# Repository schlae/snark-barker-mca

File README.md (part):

# Snark Barker MCA - A Sound Blaster Compatible for Micro Channel Computers!

Do you desperately want a sound card for playing games on your Micro Channel-based IBM PS/2 computer--a system designed for serious business purposes? Do you not want to pay the ludicrous auction prices for the rare Sound Blaster MCV cards? Well, despair no longer: the Snark Barker MCA has arrived!

The Snark Barker MCA is a Sound Blaster-compatible sound card designed specifically for computers that use the Micro Channel bus. It supports Ad Lib synthesis, digital sound playback and recording, a standard PC joystick, and SB MIDI.

All of the components are readily available. In the bill of materials, Mouser part numbers are listed where available. The Yamaha synthesis chips may be obtained from a variety of sources in China, but they are not guaranteed to work, so I recommend getting 1 or 2 extras just in case. The same goes for the NE558. Note: A user reports that a Signetics NE558 with a date code of 8825VI that seems to be commonly available from China does not actually work. If you can't find any working 558 chips, try building [my replacement that uses four 555 chips](https://oshpark.com/shared_projects/zHGURt7g).

[Schematic](https://github.com/schlae/snark-barker-mca/blob/master/SnarkBarkerMCA.pdf)

[Bill of Materials](https://github.com/schlae/snark-barker-mca/blob/master/SnarkBarkerMCA.csv)

Please note that the 0.1" header pins are *not* listed on the BOM. They are standard breakaway headers. Headers J2, J4, J5, and J6 are optional and only useful for people who want to connect a logic analyzer to the bus for CPLD debugging.

The CMS chips U14 and U15 should not be installed since CMS functionality is not implemented at this time. Other devices listed as "DNI" are to be left empty with no component soldered in place.

Logic chips are all specified as AHCT, but ALS or ACT may also be used. Do not use LS or HCT devices, particularly for U2, since Micro Channel is a much faster bus than ISA and this logic is not quite fast enough to meet the timing margins. Bipolar families like F or S devices use excessive amounts of power but can be used in a pinch.

[Fab Files](https://github.com/schlae/snark-barker-mca/blob/master/fab/SnarkBarkerMCA-Rev2.zip)

## Fabrication Notes
This is a 4-layer board. The order of the two inner layers does not matter, but typically it goes F\_Cu, In1\_Cu, In2\_Cu, and B\_Cu. The board dimensions are 11.5 inches (292.1mm) by 3.475 inches (88.265mm).

When ordering the board, you **must** specify a card edge bevel of 20 degrees (details of the bevel are included in the Dwgs.User layer). This is **not** optional! The contacts in the Micro Channel socket are easily bent if you attempt to insert a card with no bevel. [Don't believe me? See this page.](https://www.ardent-tool.com/RS6000/RS6000_9-K.html#ECA265)

Ideally you should use selective gold plating (hard gold) for the edge fingers, but this can get expensive for small orders. ENIG will work but the gold will rub off fairly quickly.

For the soldermask color, pick whatever you want!

## Assembly Notes
I recommend soldering the CPLD (U31), the voltage regulator (U32), and the associated surface mount capacitors before you solder in the remaining components. You can do this by hand with a pencil iron or you can use a reflow process, but be aware that the board is too long to fit in the small hobbyist reflow ovens.

***Be sure the CPLD is soldered in the right way around! Compare it with my photo of the card to be sure you have it right!***

Inspect the CPLD's solder joints carefully with a microscope to make sure you don't have any bad connections or solder bridges. This can save you a lot of grief later on.

Install sockets for the Yamaha chips U9 and U10 in case you get one that doesn't work and need to replace it.

## Bracket
MCA brackets are no longer available. You have a few options:
- Remove the brackets from an existing card, like a token ring card or something common
- 3D print the bracket
- Use the card without a bracket at all

If you want to print your own brackets, here are STL files of the front panel bracket and the rear bracket.

[Front bracket](https://github.com/schlae/snark-barker-mca/blob/master/mech/SnarkBarkerMCABracket3D.STL)

[Rear bracket](https://github.com/schlae/snark-barker-mca/blob/master/mech/MCARearBracket.STL)

For best results, use high quality filament and a layer height of 0.16mm or better. If you print using blue filament, the color will match the original IBM brackets.

The front bracket should be oriented so that the front face of the bracket is facing towards the bed of the printer. The rear bracket should be oriented so its large flat spot (parallel to the card) faces the bed.

To secure the bracket to the card, you need two screws, and you have several options:
- 2-56 pan-head screws, 3/16" long, McMaster Carr 91772A076 or similar. These work but aren't the strongest.
- Number 2 thread forming screws, 3/16" long, McMaster Carr 99461A710 or similar. These should grip the plastic tightly (TODO: untested).
- There may be equivalent metric options but this requires experimentation. Please let me know if you find a fastener that works well.

## The Firmware
There are two ways to get a programmed 80C51 chip for the Snark Barker MCA. One is to purchase a SB 2.0 DSP chip from China and put it in a 44-PLCC to 40-DIP adapter. This works fine and provides the largest feature set.

Another option is to buy a blank Atmel 89S51 (as listed in the BOM) and program it with [this HEX file](https://github.com/schlae/snark-barker/blob/master/firmware/sb.hex).

## CPLD Notes
The Snark Barker MCA uses a CPLD (Complex Programmable Logic Device) to interface between the Micro Channel bus and the rest of the card's digital logic. This CPLD implements port IO, interrupts, DMA, and the card setup and POS (Programmable Option Select) systems.

The CPLD must be programmed with the bitstream before you can use the card.
[You can find the bitstream here.](https://github.com/schlae/snark-barker-mca/blob/master/verilog/mcsb.jed)

I've had good luck using the Linux command line program 'xc3sprog' with a FTDI FT2232H Mini Module [datasheet here](https://www.ftdichip.com/Support/Documents/DataSheets/Modules/DS_FT2232H_Mini_Module.pdf).

Wiring for the FT2232H mini module:

| Point 1    | Point 2          | Description           |
| ---------- | ---------------- | --------------------- |
| CN2 pin 1  | CN2 pin 11       | V3V3 to VIO strap     |
| CN3 pin 1  | CN3 pin 3        | VBUS to VCC strap     |
| CN2 pin 3  | CN3 pin 12       | V3V3 to VIO strap (2) |
| CN2 pin 5  | JTAG cable pin 6 | V3V3 to Snark Barker (optional) |
| CN2 pin 2  | JTAG cable pin 5 | GND                   |
| CN2 pin 7  | JTAG cable pin 4 | AD0, aka TCK          |
| CN2 pin 9  | JTAG cable pin 3 | AD2, aka TDO          |
| CN2 pin 10 | JTAG cable pin 2 | AD1, aka TDI          |
| CN2 pin 12 | JTAG cable pin 1 | AD3, aka TMS          |

You need to provide external power to the Snark Barker through the 3.3V wire on the programming header. The optional wire does this, or you can use a bench supply.

I obtained xc3sprog [here](https://github.com/matrix-io/xc3sprog). You can compile and run this program on a Raspberry Pi to use the Pi GPIO lines instead of the FTDI mini module. In my case, I chose to patch it (TBD) to remove references to the Pi GPIO library and ran it on a regular Linux PC.

Using the FTDI mini module, programming is quite simple. Connect the cable to
the assembled Snark Barker board, then run the following command. You can do this with just the CPLD, programming header, and surface mount capacitors--there's no need to have any of the other components soldered in place for this step.

`xc3sprog -c ftdi -v mcadlib.jed`

If you run into issues with the cable not being detected, check your udev rules.
In theory you could run xc3sprog as root, but that's bad practice. ;)

### Building the CPLD Project
If you're feeling particularly masochistic, you can try building the CPLD project using the Xilinx ISE Webpack tools. Because the ISE Webpack only supports Ubuntu 14.7, it's simplest to run the program from a Docker container. I use [docker-xilinx](https://github.com/jimmo/docker-xilinx).

### How the CPLD Works
This isn't meant to be an exhaustive tutorial on how Micro Channel works ([you can find a tutorial here](https://github.com/schlae/mca-tutorial)). Functions provided by the CPLD include:
- Card setup and POS
- Address decoding logic
- Bus logic interface to the YM3812
- Wait state logic for the YM3812 interface
- Interrupt logic
- DMA state machine including arbitration logic

Each card implements several 8-bit registers (POS registers). Two of these registers are fixed and implement the 16-bit card ID value, which is how the BIOS and the reference disk software identify the card. The remaining POS registers can be used for any configuration-related function and are designed to replace configuration jumpers. The meanings of each register bit are up to the card designer, with the exception of a reserved bit that is used by the BIOS to enable or disable a card; this way, the BIOS can resolve conflicts automatically. Typically POS register bits control IO and memory address assignments, IRQ lines, and so forth.

The CPLD implements the two required ID registers as well as two additional POS registers. The first contains only a single bit -- the card enable signal. The second register controls the IO port setting, the IRQ and DMA channel settings, and the joystick port enable bit.

When you add a new card to a MCA bus system, the BIOS detects the new card and requires you to run the reference disk configuration program. This program searches for an ADF file associated with the new card. The ADF file is human-readable text that tells the BIOS which I/O address, IRQ, etc match up with each POS register bit. The reference disk program uses this information to find a configuration for all the cards in the computer so that none of them conflict with each other. When it's done, it writes the raw POS register values along with the card ID values to the battery-backed SRAM on the motherboard.

## Compatibility
The Snark Barker MCA has been tested on some models of PS/2. More to be added as
people provide test reports.

| Computer           | Model    | CPU          | Compatible ? |
| ------------------ | -------- | ------------ | ------------ |
| IBM PS/2 Model 50Z | 8550-031 | 80286-10     | Yes          |
| IBM PS/2 Model 55SX | 8555-X31 | 486SXLC2    | Yes          |
| IBM PS/2 Model 56  | 9556-KB6 | 80486SLC2-50 | Partial(1)   |
| IBM PS/2 Model 70  | 8570-E21 | 80386DX-16   | Yes          |
| IBM PS/2 Model 70  | 8570-B21 | 80486DX2-50  | Yes(1)       |
| IBM PS/2 Model P70 | 8573-061 | 80386DX-20   | Yes          |
| IBM PS/2 Model P75 | 8573-401 | 486DX2-66    | Yes(5)       |
| IBM PS/2 Model 80  | 8580-071 | 80386DX-16   | Yes(4)       |
| IBM PS/2 Model 95  | 8595     | 486DX2-50    | Yes(1)       |
| IBM PS/2 Model 95  | 9595     | Pentium-90   | Yes(3)       |
| NCR System 3400    | 3433     | 486DX2-66    | Yes          |
| NCR System 3400    | 3421     | 386SX-20     | Issues(2)    |

Note 1: See the *Machine Specific Notes* section below for more details about this configuration.

Note 2: Some problems reported with the NCR 3421 possibly due to a conflict with the onboard SCSI. Further investigation is needed.

Note 3: The Ad Lib detection routine used by some games is reported not to work

Note 4: There is one report of the Plaid Bib (the ancestor to this card) behaving erratically in this model of PS/2. However I have not observed any issues with the Snark Barker MCA.

Note 5: Machine has LAN Adapter/A installed.

If you build the card and try it out, please let me know how it went. **Be sure to give me the full part number of your computer along with any installed options (3rd-party planar, memory cards, etc).** If you're located in Silicon Valley, you could also loan me (or even give me!) a computer not on this list and I will test for compatibility myself.

## Machine Specific Notes

### IBM PS/2 Model 56 486SLC2 (9556-KB6)
Configuration: No cards installed.

The joystick port conflicts with the SCSI host that is built into the planar and must be disabled.

### IBM PS/2 Model 70 486 (8570-B21)
The configuration tested included
- 8MB RAM (on the planar)
- ESDI hard drive with DOS 6.22 and Windows 3.11 installed
- Buslogic BT640A SCSI card
- IBM XGA-2 video card

Although not fully understood, this configuration experiences what appear to be IRQ conflicts. The Micro Channel bus allows IRQ sharing, but not all software supports this correctly, so it may be related to that. "Doom" only works when using IRQ2. A workaround is to replace the default DOS4GW DOS extender with the DOS32A extender; this allows IRQ5 and IRQ7 to work correctly.

The Windows Sound Blaster driver crashes unless it is replaced with the driver recommended by Creative Labs for the SB Pro MCV. "VDMAD.386" is in the SB Pro MCV driver pack.

```
Some PS/2 machines experience a "Bus timeout error" when running Windows
3.1 in enhanced mode.  If you have this problem, Copy VDMAD.386 to your 
WINDOWS\SYSTEM sub-directory and change the following line under the [386Enh]
section in your SYSTEM.INI file.
[386Enh]
;change this line
DEVICE=*VDMAD
;to this line
DEVICE=VDMAD.386
```

You can also fix it by first starting Windows in standard mode, `win /s`, exit, and then start Windows in enhanced mode `win` as you normally would.

### IBM PS/2 Model 95 486DX2-50 (8595)
The joystick seems to conflict with something else and the setup program turns it off.

Getting Doom to run is slightly tricky and requires a hack. It only worked when IRQ was set to 5 and DOS4GW was replaced with DOS32A, but this version doesn't properly initialize the sound card. The hack is this:
- Make a copy of DOOM.EXE: `copy doom.exe doom_p.exe`
- Apply the DOS32A patch: `sb /r doom_p.exe`
- Run the original first: `doom` and let it crash back to the DOS prompt.
- Run the patched executable: `doom_p`

## Installation
You will need the ADF (adapter description file) in order to set up the Snark Barker MCA on your Micro Channel computer.

[Snark Barker MCA ADF](https://github.com/schlae/snark-barker-mca/blob/master/@5085.ADF)

Place the file on a 3 1/2" floppy disk. After you install the card and boot
the computer, it will detect that a new card has been installed and prompt
you to insert the reference disk. Do this and follow the prompts. When the
setup utility asks you to insert the option disk, use the one that contains
the ADF file. After the setup utility configures the card, it will prompt
you to reboot the machine.

Plug your line-level audio amplifier input into the card's 3mm audio jack nearest the joystick port. The other audio jack above that one is for the microphone input.

Once that's finished, try out the Snark Barker MCA with your favorite game!

## Troubleshooting
Hoo boy, this one is a doozie. Someone once told me
> At Creative Labs tech support we would always get a sinking feeling whenever someone said they had a SoundBlaster MCA. Guaranteed at least a 45 minute call. Weekly average call time blown straight to hell.

Keep in mind that Micro Channel systems can be difficult to troubleshoot due to the large number of possible configurations and the varied implementations of the bus. Not all games will even work on some PS/2 systems even without a sound card!

Here are a few things to try out first before you starting really digging in:
- Is the CPLD soldered in correctly, with no solder bridges? Did you program it?
- Are there potentially bad or fake chips? Some users have reported issues with fake NE555s or fake 74ALS245 chips.
- Did you program and install the 8051 (DSP)?
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
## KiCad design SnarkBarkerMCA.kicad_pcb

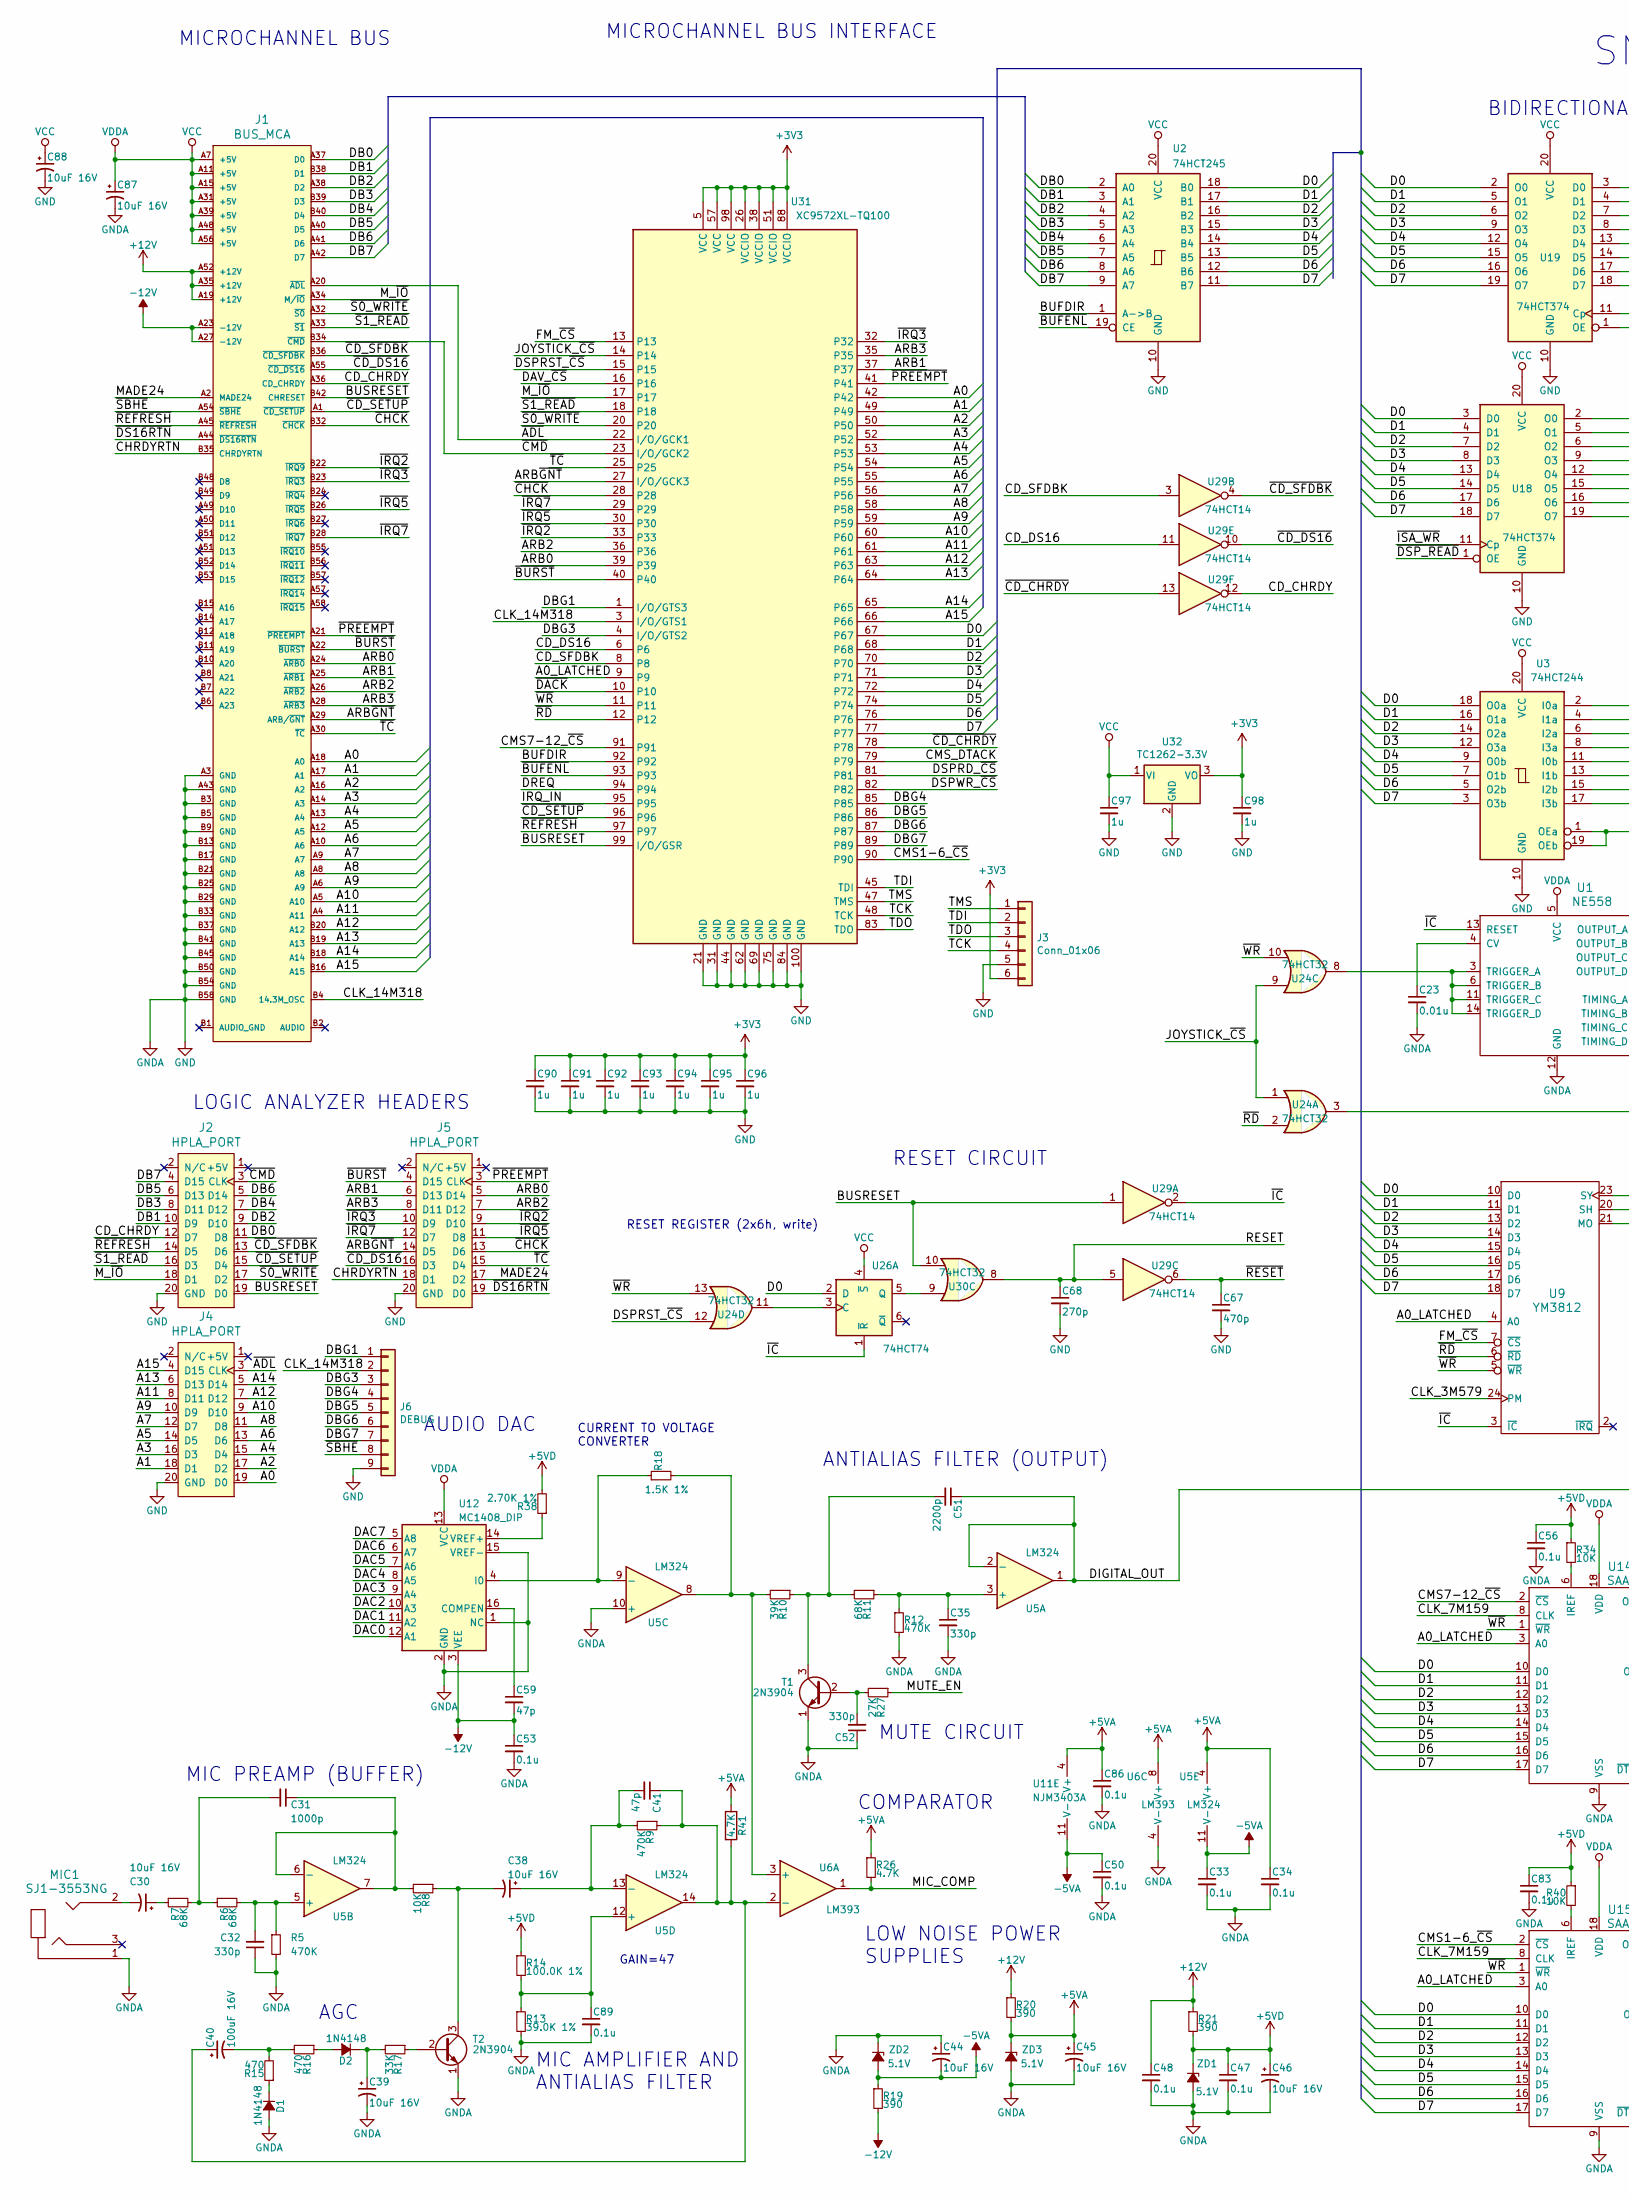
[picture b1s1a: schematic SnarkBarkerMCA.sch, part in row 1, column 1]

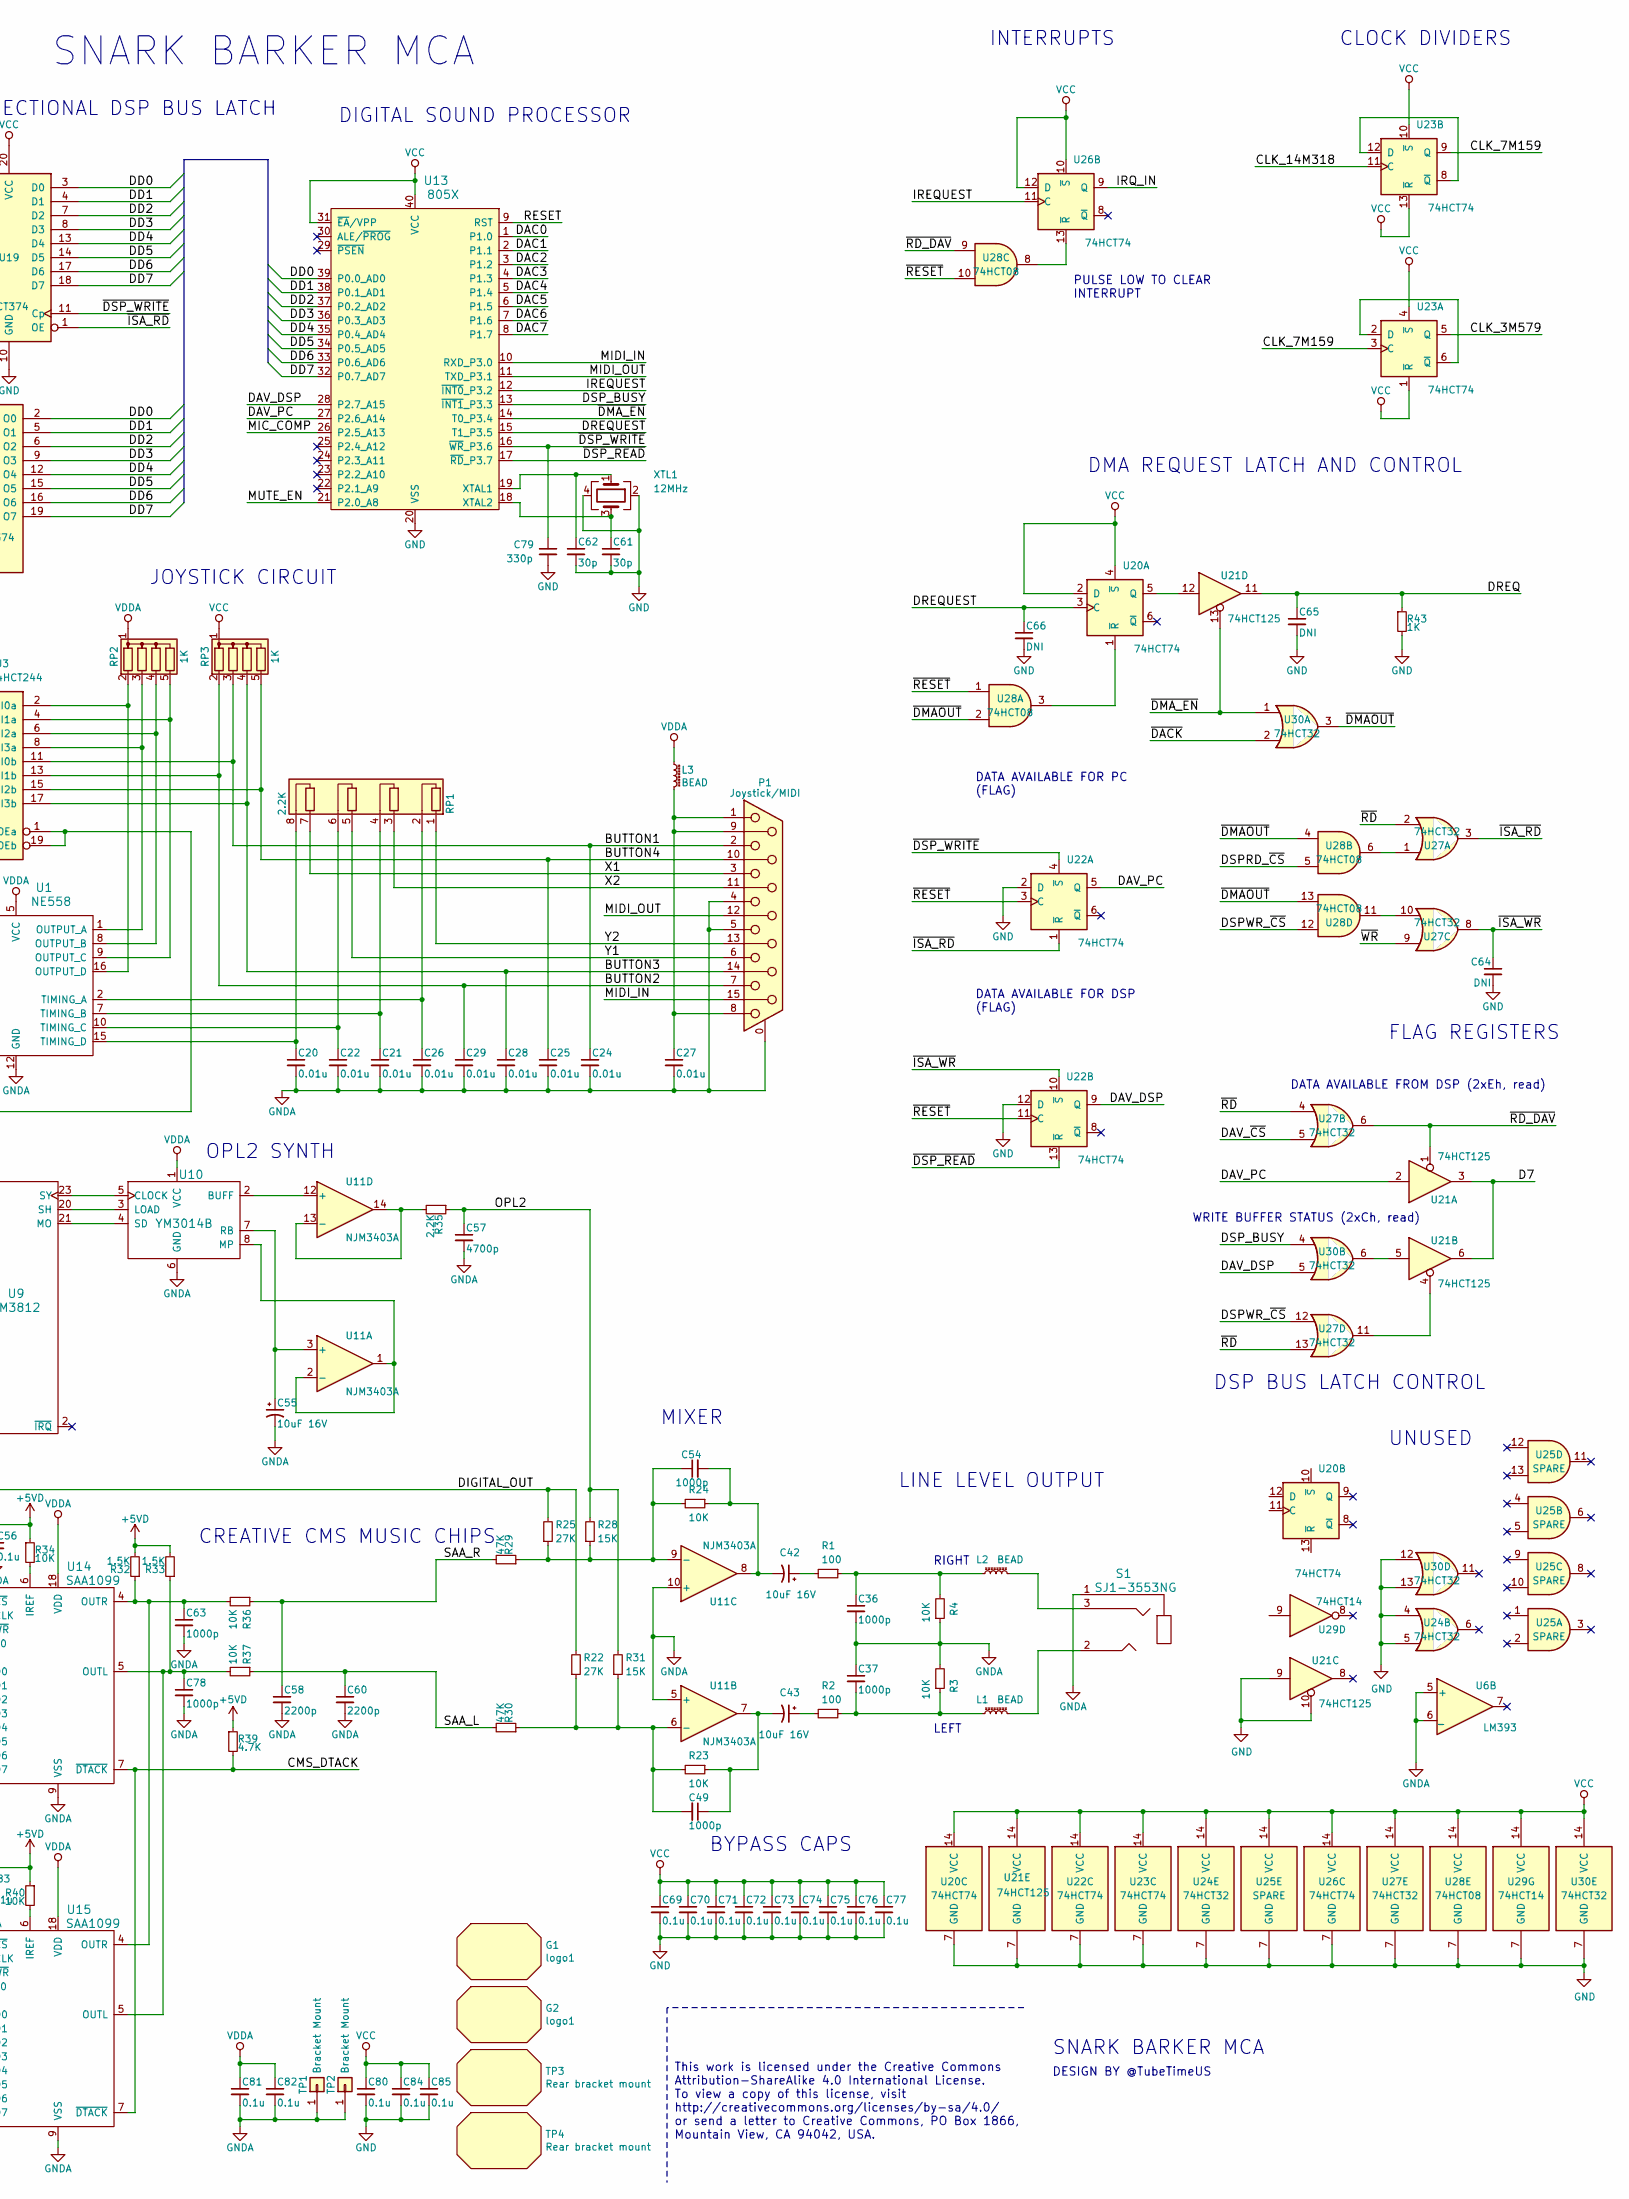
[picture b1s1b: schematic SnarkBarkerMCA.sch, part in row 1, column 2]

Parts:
C20, C21, C22, C23, C24, C25, C26, C27, C28, C29: 0.01u; SB_C_DISC_200; Mouser 810-FG28X7R1H103KNT0
C30, C38, C39, C42, C43, C44, C45, C46, C55, C87, C88: 10uF 16V; SB_C_RADIAL_75_150; Mouser 667-ECA-1CM100I
C31, C36, C37, C49, C54, C63, C78: 1000p; SB_C_DISC_200; Mouser 810-FG28X7R1H102KNT6
C32, C35, C52, C79: 330p; SB_C_DISC_200; Mouser 810-FG28C0G1H331JNT6
C33, C34, C47, C48, C50, C53, C56, C69, C70, C71, C72, C73, C74, C75, C76, C77, C80, C81, C82, C83, C84, C85, C86, C89: 0.1u; SB_C_AXIAL_275; Mouser 581-SA105E104M
C40: 100uF 16V; SB_C_RADIAL_100_320; Mouser 667-ECA-1CM101I
C41, C59: 47p; SB_C_DISC_200; Mouser 810-FG28C0G1H470JNT6
C51, C58, C60: 2200p; SB_C_DISC_200; Mouser 810-FG28X7R1H222KNT6
C57: 4700p; SB_C_DISC_200; Mouser 810-FG28C0G1H472JNT6
C61, C62: 30p; SB_C_DISC_200; Mouser 810-FG28C0G1H270JNT6
C64, C65, C66: DNI; SB_C_DISC_200
C67: 470p; SB_C_DISC_200; Mouser 810-FG28C0G1H471JNT6
C68: 270p; SB_C_DISC_200; Mouser 810-FG28C0G1H271JNT0
C90, C91, C92, C93, C94, C95, C96, C97, C98: 1u; CAPC2012X55; Mouser 187-CL21B105KAFNNNE
D1, D2: 1N4148; SB_D_AXIAL_400; Mouser 512-1N4148
G1, G2: logo1; Snark_BarkerMCA
J1: BUS_MCA
J2, J4, J5: HPLA_PORT; Pin_Header_Straight_2x10_Pitch2.54mm
J3: Conn_01x06; Pin_Header_Straight_1x06_Pitch2.54mm
J6: DEBUG; Pin_Header_Straight_1x09_Pitch2.54mm
L1, L2, L3: BEAD; SB_L_AXIAL_500; Mouser 623-2743004111
MIC1: SJ1-3553NG; SB_SJ1-3553; Mouser 490-SJ1-3553NG
P1: Joystick/MIDI; SB_DB15_152-3415; Mouser 152-3415
R1, R2: 100; SB_R_AXIAL_400; Mouser 603-CFR-25JB-52-100R
R3, R4, R8, R23, R24, R34, R36, R37, R40: 10K; SB_R_AXIAL_400; Mouser 603-CFR-25JB-52-10K
R5, R9, R12: 470K; SB_R_AXIAL_400; Mouser 603-CFR-25JR-52470K
R6, R7, R11: 68K; SB_R_AXIAL_400; Mouser 603-CFR-25JB-52-68K
R10: 39K; SB_R_AXIAL_400; Mouser 603-CFR-25JB-52-39K
R13: 39.0K 1%; SB_R_AXIAL_400; Mouser 603-MFR-25FBF52-39K
R14: 100.0K 1%; SB_R_AXIAL_400; Mouser 603-MFR-25FBF52-100K
R15, R16: 470; SB_R_AXIAL_400; Mouser 603-CFR-25JB-52-470R
R17: 33K; SB_R_AXIAL_400; Mouser 603-CFR-25JB-52-33K
R18: 1.5K 1%; SB_R_AXIAL_400; Mouser 603-MFR-25FBF52-1K5
R19, R20, R21: 390; SB_R_AXIAL_400; Mouser 603-CFR-25JB-52-390R
R22, R25, R27: 27K; SB_R_AXIAL_400; Mouser 603-CFR-25JB-52-27K
R26, R39, R41: 4.7K; SB_R_AXIAL_400; Mouser 603-CFR-25JB-52-4K7
R28, R31: 15K; SB_R_AXIAL_400; Mouser 603-CFR-25JB-52-15K
R29, R30: 47K; SB_R_AXIAL_400; Mouser 603-CFR-25JB-52-47K
R32, R33: 1.5K; SB_R_AXIAL_400; Mouser 603-CFR-25JB-52-1K5
R35: 2.2K; SB_R_AXIAL_400; Mouser 603-CFR-25JB-52-2K2
R38: 2.70K 1%; SB_R_AXIAL_400; Mouser 603-MFR-25FBF52-2K7
R43: 1K; SB_R_AXIAL_400; Mouser 603-CFR-25JR-521K
RP1: 2.2K; SB_RP_4B; Mouser 652-4608X-AP2-222LF
RP2, RP3: 1K; SB_RP_4C; Mouser 652-4605X-AP1-102LF
S1: SJ1-3553NG; SB_SJ1-3553; Mouser 490-SJ1-3553NG
T1, T2: 2N3904; SB_TO92; Mouser 833-2N3904-AP
TP1, TP2: Bracket Mount; MH_125_200
TP3, TP4: Rear bracket mount; MH_125
U1: NE558; SB_DIP16_300
U2: 74HCT245; SB_DIP20_300; Mouser 595-SN74HCT245NE4
U3: 74HCT244; SB_DIP20_300; Mouser 595-SN74HCT244NE4
U5: LM324; SB_DIP14_300; Mouser 926-LM324AN/NOPB
U6: LM393; SB_DIP8_300; Mouser 595-LM393P
U9: YM3812; SB_DIP24_600
U10: YM3014B; SB_DIP8_300
U11: NJM3403A; SB_DIP14_300; Mouser 513-NJM3403AD
U12: MC1408_DIP; SB_DIP16_300; Mouser 926-DAC0808LCN/NOPB
U13: 805X; SB_DIP40_600; Mouser 556-A89S51-24PU
U14, U15: SAA1099; SB_DIP18_300
U18, U19: 74HCT374; SB_DIP20_300; Mouser 595-SN74HCT374N
U20, U22, U23, U26: 74HCT74; SB_DIP14_300; Mouser 595-SN74HCT74NE4
U21: 74HCT125; SB_DIP14_300; Mouser 595-SN74HCT125NE4
U24, U27, U30: 74HCT32; SB_DIP14_300; Mouser 595-SN74HCT32NE4
U25: SPARE; SB_DIP14_300
U28: 74HCT08; SB_DIP14_300; Mouser 595-SN74HCT08NE4
U29: 74HCT14; SB_DIP14_300; Mouser 595-SN74HCT14N
U31: XC9572XL-TQ100; TQFP50P1600X1600X140-100; Mouser 217-9572XL-10TQG100C
U32: TC1262-3.3V; SOT230P700X170-3; Mouser 579-TC1262-3.3VDB
XTL1: 12MHz; SB_XTAL_HC49U_RA; Mouser 815-AB-12-B2
ZD1, ZD2, ZD3: 5.1V; SB_D_AXIAL_400_ALT; Mouser 78-1N5231B-TAP

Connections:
+3V3: C90.1, C91.1, C92.1, C93.1, C94.1, C95.1, C96.1, C98.1, J3.6, U31.5 (VCC), U31.26 (VCCIO), U31.38 (VCCIO), U31.51 (VCCIO), U31.57 (VCC), U31.88 (VCCIO), U31.98 (VCC), U32.3 (VO)
+5VA: C34.1, C45.1, C86.1, R20.2, R26.1, R41.1, U5.4 (V+), U6.8 (V+), U11.4 (V+), ZD3.1 (K)
+5VD: C46.1, C47.1, C56.1, C83.1, R14.1, R21.2, R32.2, R33.2, R34.1, R38.2, R39.1, R40.1, ZD1.1 (K)
+12V: C48.1, J1.A19 (+12V), J1.A35 (+12V), J1.A52 (+12V), R20.1, R21.1
-5VA: C33.1, C44.2, C50.1, R19.1, U5.11 (V-), U11.11 (V-), ZD2.2 (A)
-12V: C53.1, C59.2, J1.A23 (-12V), J1.A27 (-12V), R19.2, U12.3 (VEE)
/A0: J1.A18 (A0), J4.19 (D0), U31.42
/A0_LATCHED: U9.4 (A0), U14.3 (A0), U15.3 (A0), U31.9
/A1: J1.A17 (A1), J4.18 (D1), U31.49
/A2: J1.A16 (A2), J4.17 (D2), U31.50
/A3: J1.A14 (A3), J4.16 (D3), U31.52
/A4: J1.A13 (A4), J4.15 (D4), U31.53
/A5: J1.A12 (A5), J4.14 (D5), U31.54
/A6: J1.A10 (A6), J4.13 (D6), U31.55
/A7: J1.A9 (A7), J4.12 (D7), U31.56
/A8: J1.A8, J4.11 (D8), U31.58
/A9: J1.A6 (A9), J4.10 (D9), U31.59
/A10: J1.A5 (A10), J4.9 (D10), U31.60
/A11: J1.A4 (A11), J4.8 (D11), U31.61
/A12: J1.B20 (A12), J4.7 (D12), U31.63
/A13: J1.B19 (A13), J4.6 (D13), U31.64
/A14: J1.B18 (A14), J4.5 (D14), U31.65
/A15: J1.B16 (A15), J4.4 (D15), U31.66
/ARB0: J1.A24 (~ARB0), J5.5 (D14), U31.39
/ARB1: J1.A25 (~ARB1), J5.6 (D13), U31.37
/ARB2: J1.A26 (~ARB2), J5.7 (D12), U31.36
/ARB3: J1.A28 (~ARB3), J5.8 (D11), U31.35
/ARB~GNT: J1.A29 (ARB/~GNT), J5.14 (D5), U31.27 (I/O/GCK3)
/BUFDIR: U2.1 (A->B), U31.92
/BUSRESET: J1.B42 (CHRESET), J2.19 (D0), U29.1, U30.10, U31.99 (I/O/GSR)
/BUTTON1: C24.1, P1.2, RP3.3 (R2), U3.11 (I0b)
/BUTTON2: C29.1, P1.7, RP3.2 (R1), U3.13 (I1b)
/BUTTON3: C28.1, P1.14, RP3.4 (R3), U3.17 (I3b)
/BUTTON4: C25.1, P1.10, RP3.5 (R4), U3.15 (I2b)
/CD_CHRDY: J1.A36 (CD_CHRDY), J2.12 (D7), U29.12
/CD_DS16: U29.11, U31.6
/CD_SFDBK: U29.3, U31.8
/CHRDYRTN: J1.B35 (CHRDYRTN), J5.18 (D1)
/CLK_3M579: U9.24 (PM), U23.5 (Q)
/CLK_7M159: U14.8 (CLK), U15.8 (CLK), U23.3 (C), U23.9 (Q)
/CLK_14M318: J1.B4 (14.3M_OSC), J6.2, U23.11 (C), U31.3 (I/O/GTS1)
/CMS1-6_~CS: U15.2 (~CS), U31.90
/CMS7-12_~CS: U14.2 (~CS), U31.91
/CMS_DTACK: R39.2, U14.7 (~DTACK), U15.7 (~DTACK), U31.79
/D0: U2.18 (B0), U3.18 (O0a), U9.10 (D0), U14.10 (D0), U15.10 (D0), U18.3 (D0), U19.2 (O0), U26.2 (D), U31.67
/D1: U2.17 (B1), U3.16 (O1a), U9.11 (D1), U14.11 (D1), U15.11 (D1), U18.4 (D1), U19.5 (O1), U31.68
/D2: U2.16 (B2), U3.14 (O2a), U9.13 (D2), U14.12 (D2), U15.12 (D2), U18.7 (D2), U19.6 (O2), U31.70
/D3: U2.15 (B3), U3.12 (O3a), U9.14 (D3), U14.13 (D3), U15.13 (D3), U18.8 (D3), U19.9 (O3), U31.71
/D4: U2.14 (B4), U3.9 (O0b), U9.15 (D4), U14.14 (D4), U15.14 (D4), U18.13 (D4), U19.12 (O4), U31.72
/D5: U2.13 (B5), U3.7 (O1b), U9.16 (D5), U14.15 (D5), U15.15 (D5), U18.14 (D5), U19.15 (O5), U31.74
/D6: U2.12 (B6), U3.5 (O2b), U9.17 (D6), U14.16 (D6), U15.16 (D6), U18.17 (D6), U19.16 (O6), U31.76
/D7: U2.11 (B7), U3.3 (O3b), U9.18 (D7), U14.17 (D7), U15.17 (D7), U18.18 (D7), U19.19 (O7), U21.3, U21.6, U31.77
/DAC0: U12.12 (A1), U13.1 (P1.0)
/DAC1: U12.11 (A2), U13.2 (P1.1)
/DAC2: U12.10 (A3), U13.3 (P1.2)
/DAC3: U12.9 (A4), U13.4 (P1.3)
/DAC4: U12.8 (A5), U13.5 (P1.4)
/DAC5: U12.7 (A6), U13.6 (P1.5)
/DAC6: U12.6 (A7), U13.7 (P1.6)
/DAC7: U12.5 (A8), U13.8 (P1.7)
/DAV_DSP: U13.28 (P2.7_A15), U22.9 (Q), U30.5
/DAV_PC: U13.27 (P2.6_A14), U21.2, U22.5 (Q)
/DAV_~CS: U27.5, U31.16
/DB0: J1.A37 (D0), J2.11 (D8), U2.2 (A0)
/DB1: J1.B38 (D1), J2.10 (D9), U2.3 (A1)
/DB2: J1.A38 (D2), J2.9 (D10), U2.4 (A2)
/DB3: J1.B39 (D3), J2.8 (D11), U2.5 (A3)
/DB4: J1.B40 (D4), J2.7 (D12), U2.6 (A4)
/DB5: J1.A40 (D5), J2.6 (D13), U2.7 (A5)
/DB6: J1.A41 (D6), J2.5 (D14), U2.8 (A6)
/DB7: J1.A42 (D7), J2.4 (D15), U2.9 (A7)
/DBG1: J6.1, U31.1 (I/O/GTS3)
/DBG3: J6.3, U31.4 (I/O/GTS2)
/DBG4: J6.4, U31.85
/DBG5: J6.5, U31.86
/DBG6: J6.6, U31.87
/DBG7: J6.7, U31.89
/DD0: U13.39 (P0.0_AD0), U18.2 (O0), U19.3 (D0)
/DD1: U13.38 (P0.1_AD1), U18.5 (O1), U19.4 (D1)
/DD2: U13.37 (P0.2_AD2), U18.6 (O2), U19.7 (D2)
/DD3: U13.36 (P0.3_AD3), U18.9 (O3), U19.8 (D3)
/DD4: U13.35 (P0.4_AD4), U18.12 (O4), U19.13 (D4)
/DD5: U13.34 (P0.5_AD5), U18.15 (O5), U19.14 (D5)
/DD6: U13.33 (P0.6_AD6), U18.16 (O6), U19.17 (D6)
/DD7: U13.32 (P0.7_AD7), U18.19 (O7), U19.18 (D7)
/DIGITAL_OUT: C51.1, R22.2, R25.2, U5.1, U5.2 (-)
/DREQ: C65.1, R43.1, U21.11, U31.94
/DREQUEST: C66.1, U13.15 (T1_P3.5), U20.3 (C)
/DSPRD_~CS: U28.5, U31.81
/DSPRST_~CS: U24.12, U31.15
/DSPWR_~CS: U27.12, U28.12, U31.82
/DSP_BUSY: U13.13 (~INT1~_P3.3), U30.4
/FM_~CS: U9.7 (~CS), U31.13
/IREQUEST: U13.12 (~INT0~_P3.2), U26.11 (C)
/IRQ_IN: U26.9 (Q), U31.95
/JOYSTICK_~CS: U24.1, U24.9, U31.14
/MADE24: J1.A2 (MADE24), J5.17 (D2)
/MIC_COMP: R26.2, U6.1, U13.26 (P2.5_A13)
/MIDI_IN: P1.15, U13.10 (RXD_P3.0)
/MIDI_OUT: P1.12, U13.11 (TXD_P3.1)
/MUTE_EN: R27.1, U13.21 (P2.0_A8)
/M_~IO: J1.A34 (M/~IO), J2.18 (D1), U31.17
/OPL2: C57.1, R28.2, R31.2, R35.1
/RESET: C68.1, U13.9 (RST), U29.5, U30.8
/SAA_L: C60.1, R30.2, R37.1
/SAA_R: C58.1, R29.2, R36.1
/TCK: J3.4, U31.48 (TCK)
/TDI: J3.2, U31.45 (TDI)
/TDO: J3.3, U31.83 (TDO)
/TMS: J3.1, U31.47 (TMS)
/X1: P1.3, RP1.7 (R4.1)
/X2: P1.11 (P111), RP1.3 (R2.1)
/Y1: P1.6, RP1.5 (R3.1)
/Y2: P1.13, RP1.1 (R1.1)
/~ADL: J1.A20 (~ADL), J4.3 (CLK), U31.22 (I/O/GCK1)
/~BUFENL: U2.19 (CE), U31.93
/~BURST: J1.A22 (~BURST), J5.4 (D15), U31.40
/~CD_CHRDY: U29.13, U31.78
/~CD_DS16: J1.A55 (~CD_DS16), J5.16 (D3), U29.10
/~CD_SETUP: J1.A1 (~CD_SETUP), J2.15 (D4), U31.96
/~CD_SFDBK: J1.B36 (~CD_SFDBK), J2.13 (D6), U29.4
/~CHCK: J1.B32 (~CHCK), J5.13 (D6), U31.28
/~CMD: J1.B34 (~CMD), J2.3 (CLK), U31.23 (I/O/GCK2)
/~DACK: U30.2, U31.10
/~DMAOUT: U28.2, U28.4, U28.13, U30.3
/~DMA_EN: U13.14 (T0_P3.4), U21.13, U30.1
/~DS16RTN: J1.A44 (~DS16RTN), J5.19 (D0)
/~DSP_READ: U13.17 (~RD~_P3.7), U18.1 (OE), U22.13 (~R)
/~DSP_WRITE: C79.1, U13.16 (~WR~_P3.6), U19.11 (Cp), U22.4 (~S)
/~IC: U1.13 (RESET), U9.3 (~IC), U26.1 (~R), U29.2
/~IRQ2: J1.B22 (~IRQ9), J5.9 (D10), U31.33
/~IRQ3: J1.B23 (~IRQ3), J5.10 (D9), U31.32
/~IRQ5: J1.B26 (~IRQ5), J5.11 (D8), U31.30
/~IRQ7: J1.B28 (~IRQ7), J5.12 (D7), U31.29
/~ISA_RD: U19.1 (OE), U22.1 (~R), U27.3
/~ISA_WR: C64.1, U18.11 (Cp), U22.10 (~S), U27.8
/~PREEMPT: J1.A21 (~PREEMPT), J5.3 (CLK), U31.41
/~RD: U9.6 (~RD), U24.2, U27.2, U27.4, U27.13, U31.12
/~RD_DAV: U21.1, U27.6, U28.9
/~REFRESH: J1.A45 (~REFRESH), J2.14 (D5), U31.97
/~RESET: C67.1, U22.3 (C), U22.11 (C), U28.1, U28.10, U29.6
/~S0_WRITE: J1.A32 (~S0), J2.17 (D2), U31.20
/~S1_READ: J1.A33 (~S1), J2.16 (D3), U31.18
/~SBHE: J1.A54 (~SBHE), J6.8
/~TC: J1.A30 (~TC), J5.15 (D4), U31.25
/~WR: U9.5 (~WR), U14.1 (~WR), U15.1 (~WR), U24.10, U24.13, U27.9, U31.11
GND: C20.2, C21.2, C22.2, C23.2, C24.2, C25.2, C26.2, C27.2, C28.2, C29.2, C32.1, C33.2, C34.2, C35.2, C36.2, C37.1, C39.2, C44.1, C45.2, C46.2, C47.2, C48.2, C50.2, C52.1, C53.2, C55.2, C56.2, C57.2, C58.2, C60.2, C61.2, C62.2, C63.2, C64.2, C65.2, C66.2, C67.2, C68.2, C69.2, C70.2, C71.2, C72.2, C73.2, C74.2, C75.2, C76.2, C77.2, C78.2, C79.2, C80.2, C81.2, C82.2, C83.2, C84.2, C85.2, C86.2, C87.2, C88.2, C89.2, C90.2, C91.2, C92.2, C93.2, C94.2, C95.2, C96.2, C97.2, C98.2, D1.2 (A), J1.A3 (GND), J1.A43 (GND), J1.B3 (GND), J1.B5 (GND), J1.B9 (GND), J1.B13 (GND), J1.B17 (GND), J1.B21 (GND), J1.B25 (GND), J1.B29 (GND), J1.B33 (GND), J1.B37 (GND), J1.B41 (GND), J1.B45 (GND), J1.B50 (GND), J1.B54 (GND), J1.B58 (GND), J2.20 (GND), J3.5, J4.20 (GND), J5.20 (GND), J6.9, MIC1.1, P1.0 (PAD), P1.4, P1.5, R3.2, R4.1, R5.2, R12.2, R13.2, R43.2, S1.1, T1.1 (E), T2.1 (E)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
unnamed: C20.1, RP1.8 (R4.2), U1.15 (TIMING_D)
unnamed: C21.1, RP1.4 (R2.2), U1.7 (TIMING_B)
unnamed: C22.1, RP1.6 (R3.2), U1.10 (TIMING_C)
unnamed: C23.1, U1.4 (CV)
unnamed: C26.1, RP1.2 (R1.2), U1.2 (TIMING_A)
unnamed: C27.1, L3.2, P1.1, P1.8, P1.9
unnamed: C30.1, R7.1
unnamed: C30.2, MIC1.2
unnamed: C31.1, R8.2, U5.6 (-), U5.7
unnamed: C31.2, R6.1, R7.2
unnamed: C32.2, R5.1, R6.2, U5.5 (+)
unnamed: C35.1, R11.1, R12.1, U5.3 (+)
unnamed: C36.1, L2.1, R1.1, R4.2
unnamed: C37.2, L1.1, R2.1, R3.1
unnamed: C38.1, C41.2, R9.2, U5.13 (-)
unnamed: C38.2, R8.1, T2.3 (C)
unnamed: C39.1, D2.1 (K), R17.2
unnamed: C40.1, C41.1, R9.1, R41.2, U5.14, U6.2 (-)
unnamed: C40.2, R15.2, R16.2
unnamed: C42.1, R1.2
unnamed: C42.2, C54.2, R24.1, U11.8
unnamed: C43.1, R2.2
unnamed: C43.2, C49.1, R23.1, U11.7
unnamed: C49.2, R22.1, R23.2, R30.1, R31.1, U11.6 (-)
unnamed: C51.2, R10.1, R11.2, T1.3 (C)
unnamed: C52.2, R27.2, T1.2 (B)
unnamed: C54.1, R24.2, R25.1, R28.1, R29.1, U11.9 (-)
unnamed: C55.1, U10.7 (RB), U11.3 (+)
unnamed: C59.1, U12.16 (COMPEN)
unnamed: C61.1, U13.18 (XTAL2), XTL1.3
unnamed: C62.1, U13.19 (XTAL1), XTL1.1
unnamed: C63.1, R32.1, R36.2, U14.4 (OUTR), U15.4 (OUTR)
unnamed: C78.1, R33.1, R37.2, U14.5 (OUTL), U15.5 (OUTL)
unnamed: C89.1, R13.1, R14.2, U5.12 (+)
unnamed: D1.1 (K), R15.1
unnamed: D2.2 (A), R16.1
unnamed: L1.2, S1.2
unnamed: L2.2, S1.3
unnamed: R10.2, R18.2, U5.8, U6.3 (+)
unnamed: R17.1, T2.2 (B)
unnamed: R18.1, U5.9 (-), U12.4 (I0)
unnamed: R34.2, U14.6 (IREF)
unnamed: R35.2, U11.13 (-), U11.14
unnamed: R38.1, U12.14 (VREF+)
unnamed: R40.2, U15.6 (IREF)
unnamed: RP2.2 (R1), U1.16 (OUTPUT_D), U3.2 (I0a)
unnamed: RP2.3 (R2), U1.1 (OUTPUT_A), U3.8 (I3a)
unnamed: RP2.4 (R3), U1.8 (OUTPUT_B), U3.6 (I2a)
unnamed: RP2.5 (R4), U1.9 (OUTPUT_C), U3.4 (I1a)
unnamed: U1.3 (TRIGGER_A), U1.6 (TRIGGER_B), U1.11 (TRIGGER_C), U1.14 (TRIGGER_D), U24.8
unnamed: U10.2 (BUFF), U11.12 (+)
unnamed: U9.20 (SH), U10.3 (LOAD)
unnamed: U9.21 (MO), U10.4 (SD)
unnamed: U9.23 (SY), U10.5 (CLOCK)
unnamed: U10.8 (MP), U11.1, U11.2 (-)
unnamed: U20.1 (~R), U28.3
unnamed: U20.5 (Q), U21.12
unnamed: U21.4, U27.11
unnamed: U21.5, U30.6
unnamed: U23.2 (D), U23.6 (~Q)
unnamed: U23.8 (~Q), U23.12 (D)
unnamed: U3.1 (OEa), U3.19 (OEb), U24.3
unnamed: U24.11, U26.3 (C)
unnamed: U26.5 (Q), U30.9
unnamed: U26.13 (~R), U28.8
unnamed: U27.1, U28.6
unnamed: U27.10, U28.11
VCC: C69.1, C70.1, C71.1, C72.1, C73.1, C74.1, C75.1, C76.1, C77.1, C80.1, C81.1, C82.1, C84.1, C85.1, C87.1, C88.1, C97.1, J1.A7 (+5V), J1.A11 (+5V), J1.A15 (+5V), J1.A31 (+5V), J1.A39 (+5V), J1.A48 (+5V), J1.A56 (+5V), L3.1, RP2.1 (common), RP3.1 (common), U1.5 (VCC), U2.20 (VCC), U3.20 (VCC), U9.1 (VCC), U10.1 (VCC), U12.13 (VCC), U13.31 (~EA~/VPP), U13.40 (VCC), U14.18 (VDD), U15.18 (VDD), U18.20 (VCC), U19.20 (VCC), U20.2 (D), U20.4 (~S), U20.14 (VCC), U21.14 (VCC), U22.14 (VCC), U23.1 (~R), U23.4 (~S), U23.10 (~S), U23.13 (~R), U23.14 (VCC), U24.14 (VCC), U25.14 (VCC), U26.4 (~S), U26.10 (~S), U26.12 (D), U26.14 (VCC), U27.14 (VCC), U28.14 (VCC), U29.14 (VCC), U30.14 (VCC), U32.1 (VI)

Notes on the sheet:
AGC
MIC PREAMP (BUFFER)
MIC AMPLIFIER AND ANTIALIAS FILTER
GAIN=47
CURRENT TO VOLTAGE CONVERTER
AUDIO DAC
MUTE CIRCUIT
ANTIALIAS FILTER (OUTPUT)
COMPARATOR
MIXER
LINE LEVEL OUTPUT
LEFT
RIGHT
LOW NOISE POWER SUPPLIES
OPL2 SYNTH
CREATIVE CMS MUSIC CHIPS
JOYSTICK CIRCUIT
CLOCK DIVIDERS
PULSE LOW TO CLEAR INTERRUPT
FLAG REGISTERS
INTERRUPTS
DMA REQUEST LATCH AND CONTROL
MICROCHANNEL BUS INTERFACE
RESET CIRCUIT
DATA AVAILABLE FOR PC (FLAG)
DATA AVAILABLE FOR DSP (FLAG)
DATA AVAILABLE FROM DSP (2xEh, read)
WRITE BUFFER STATUS (2xCh, read)
RESET REGISTER (2x6h, write)
MICROCHANNEL BUS
DIGITAL SOUND PROCESSOR
BIDIRECTIONAL DSP BUS LATCH
DSP BUS LATCH CONTROL
UNUSED
SNARK BARKER MCA
DESIGN BY @TubeTimeUS
This work is licensed under the Creative Commons Attribution-ShareAlike 4.0 International License. To view a copy of this license, visit http://creativecommons.org/licenses/by-sa/4.0/ or send a letter to Creative Commons, PO Box 1866, Mountain View, CA 94042, USA.
BYPASS CAPS
LOGIC ANALYZER HEADERS

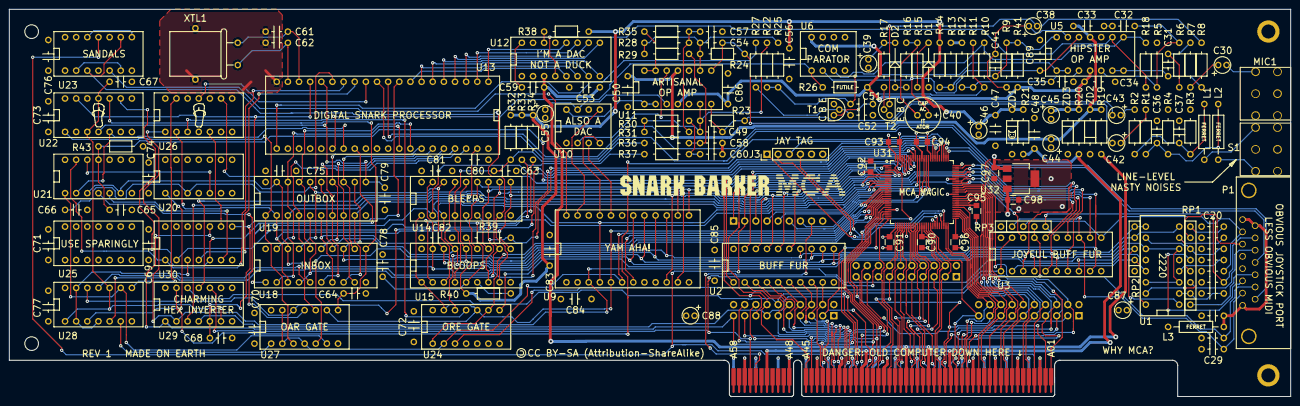
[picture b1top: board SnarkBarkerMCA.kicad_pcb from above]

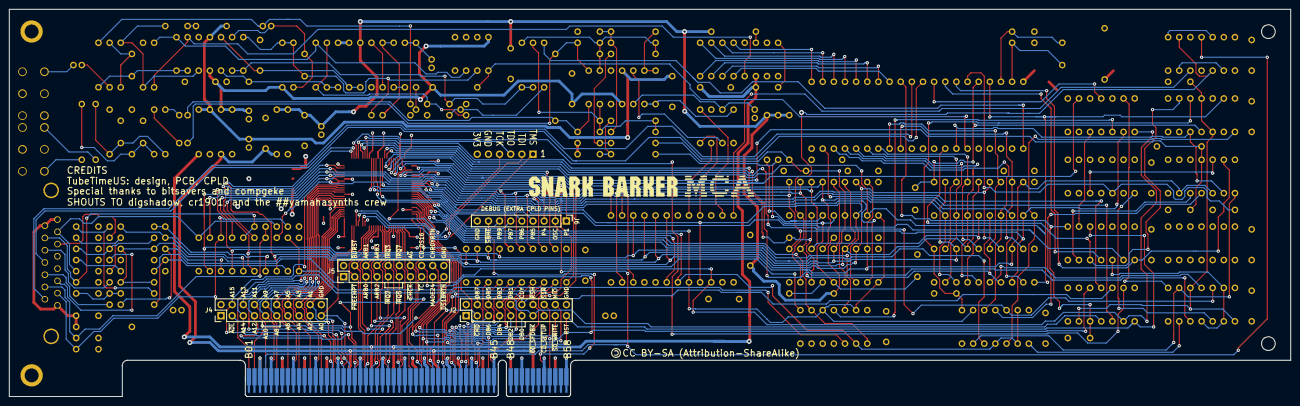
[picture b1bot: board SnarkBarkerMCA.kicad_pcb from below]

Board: 4 copper layers, 292.1 x 88.3 mm, 177 parts (5 on the bottom side), 215 nets.

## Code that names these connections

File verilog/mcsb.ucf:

#
# SB MCA CPLD Version - Constraints (pin mapping)
# Copyright (c) 2020 Eric Schlaepfer
# This work is licensed under the Creative Commons Attribution-ShareAlike 4.0
# International License. To view a copy of this license, visit
# http://creativecommons.org/licenses/by-sa/4.0/ or send a letter to Creative
# Commons, PO Box 1866, Mountain View, CA 94042, USA.
#

# Pin map
NET "adl_l" loc="P22";
NET "adl_l" BUFG=CLK;
NET "cmd" loc="P23";
NET "cmd" BUFG=CLK;

NET "arb_grant_l" loc="P27";
NET "arb_grant_l" BUFG=CLK;

NET "cden" loc="P1"; # Card enable signal for debugging (DBG1)
NET "clk14" loc="P3"; # 14.318MHz clock

NET "cd_setup_l" loc="P96";
NET "refresh" loc="P97";
NET "chck_l" loc="P28";
NET "cd_sfdbk" loc="P8";
NET "cd_ds16" loc="P6";
NET "cd_chrdy_l" loc="P78";

NET "m_io" loc="P17";
NET "s0_w_l" loc="P20";
NET "s1_r_l" loc="P18";
NET "a(0)" loc="P42";
NET "a(1)" loc="P49";
NET "a(2)" loc="P50";
NET "a(3)" loc="P52";
NET "a(4)" loc="P53";
NET "a(5)" loc="P54";
NET "a(6)" loc="P55";
NET "a(7)" loc="P56";
NET "a(8)" loc="P58";
NET "a(9)" loc="P59";
NET "a(10)" loc="P60";
NET "a(11)" loc="P61";
NET "a(12)" loc="P63";
NET "a(13)" loc="P64";
NET "a(14)" loc="P65";
NET "a(15)" loc="P66";

NET "d(0)" loc="P67";
NET "d(1)" loc="P68";
NET "d(2)" loc="P70";
NET "d(3)" loc="P71";
NET "d(4)" loc="P72";
NET "d(5)" loc="P74";
NET "d(6)" loc="P76";
NET "d(7)" loc="P77";

NET "cms_dtack_l" loc="P79";
NET "dsp_rd_cs_l" loc="P81";
NET "dsp_wr_cs_l" loc="P82";
NET "dav_cs_l" loc="P16";
NET "dsp_rst_cs_l" loc="P15";
NET "cms1_6_cs_l" loc="P90";
NET "cms7_12_cs_l" loc="P91";
NET "joy_cs_l" loc="P14";
NET "ior_l" loc="P12";
NET "iow_l" loc="P11";
NET "ym_cs_l" loc="P13";
NET "latched_a0" loc="P9";

NET "bufen_l" loc="P93";
NET "bufdir" loc="P92";

NET "chreset" loc="P99";

NET "preempt_l" loc="P41";
NET "burst_l" loc="P40";
NET "arb(0)" loc="P39";
NET "arb(1)" loc="P37";
NET "arb(2)" loc="P36";
NET "arb(3)" loc="P35";
NET "tc_l" loc="P25";
NET "dreq" loc="P94";
NET "dack_l" loc="P10";

NET "irq_2" loc="P33";
NET "irq_3" loc="P32";
NET "irq_5" loc="P30";
NET "irq_7" loc="P29";
NET "irq_in" loc="P95";

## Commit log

2020-11-29 Empty commit
2020-11-29 Fix image name
2020-11-29 Fix path to STL files
2020-11-29 Fix path to bitstream
2020-11-29 Fix path to ADF
2020-11-29 Fix ADF file extension
2020-11-29 Fix link to SBDIAG
2020-12-02 Add warning about edge bevel
2020-12-03 Add info on bracket screws
2020-12-07 Combine R41 into R26,R39 line item
2020-12-30 Update bevel link
2021-02-01 Update compatibility list
2021-02-17 Notes for model 70 486
2021-02-18 Notes for model 56 486SLC2
2021-03-30 Add PS/2 model 80 (20MHz) to compatibility list
2021-06-06 Logic chip update
2021-06-16 fixed hex prefix issue in ADF
2021-07-09 Updated 8580 entry in compatibility list
2021-07-11 Update 8595 notes
2021-08-03 add HP logic analyzer config file
2021-08-14 Add P75 to compatibility chart
2022-04-30 add 55sx to compatibility list

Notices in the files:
README.md:
License:
This work is licensed under a Creative Commons Attribution-ShareAlike 4.0
International License. See [https://creativecommons.org/licenses/by-sa/4.0/](https://creativecommons.org/licenses/by-sa/4.0/).
SnarkBarkerMCA.kicad_pcb:
Copyright (C) 2020 Tube Time
This work is licensed under a Creative Commons Attribution-ShareAlike 4.0 International
CC BY-SA (Attribution-ShareAlike)
